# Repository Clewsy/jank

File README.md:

# jank

jank is **j**ust **an**other **k**eypad.  Specifically it is a USB numeric keypad with some macro buttons.  It's kind of an evolution of another project ([macro][link_gitlab_macr0]).

Additional photos and detail can be found at [clews.pro][link_clews_jank] and [hackaday.io][link_hackaday.io_jank].

Features include:
* Uses a USB type C connector (configured to identify as a USB 2.0 device).
* 21 keys total - 17 keys configured in a standard keypad arrangement, plus an addition row of four keys across the top.
* All 21 keys can be configured as any reguglar keyboard keystroke (including media control keys) or a programmable macro.
* The keys are all mechanical keyswitches - I used gateron blues which are pin-comnpatible with [Cherry MX][link_web_cherry_mx] keyswitches.
* All the keyswitches are plate-mounted with a laser-cut stainless steel plate.  The larger '+', '0' and "Enter" keys all have cherry-style, plate-mounted stabilizers.
* There is a 3mm led beneath each keyswitch so that the legends are all back-lit.
* The LEDs are powered via a boost controller (MP3202) which is enabled by a PWM signal from the microcontroller - this allows variable brightness.  Brightness is set by a tact switch on the bottom of the unit.  Pushing the switch cycles the LEDs from off through increasing levels of brightness and a pulsing effect with three different speeds.
* There is a single smd LED on the bottom of the unit that is programmed to function as the NUM LOCK indicator.

Although any key can be configured to function as any keystroke or macro, I use jank with my laptop as a traditional numerical keypad.  Only the top four keys are configured as macros.

Proudly mentioned at [hackaday.com][link_hackaday_jank].

*********************************

To do:

- [X] Hardware
    - [X] Parts selection.
    - [X] Schematic design.
    - [X] PCB layout design.
    - [X] Parts order.
    - [X] PCB assembly.
    - [X] Enclosure.
- [X] Firmware
    - [X] LED control.
    - [X] Regular keystrokes.
    - [X] Num lock LED.
    - [X] Simple macros.
    - [X] Complex macros.

*********************************

![The completed jank.][image_jank]

[link_clews_jank]:https://clews.pro/projects/jank.php
[link_gitlab_macr0]:https://gitlab.com/clewsy/macr0
[link_hackaday_jank]:https://hackaday.com/2021/06/08/custom-num-pad-does-double-duty-as-macro-pad/
[link_hackaday.io_jank]:https://hackaday.io/project/180104-jank
[link_web_cherry_mx]:https://www.cherrymx.de/en

[image_jank]:images/jank.jpg

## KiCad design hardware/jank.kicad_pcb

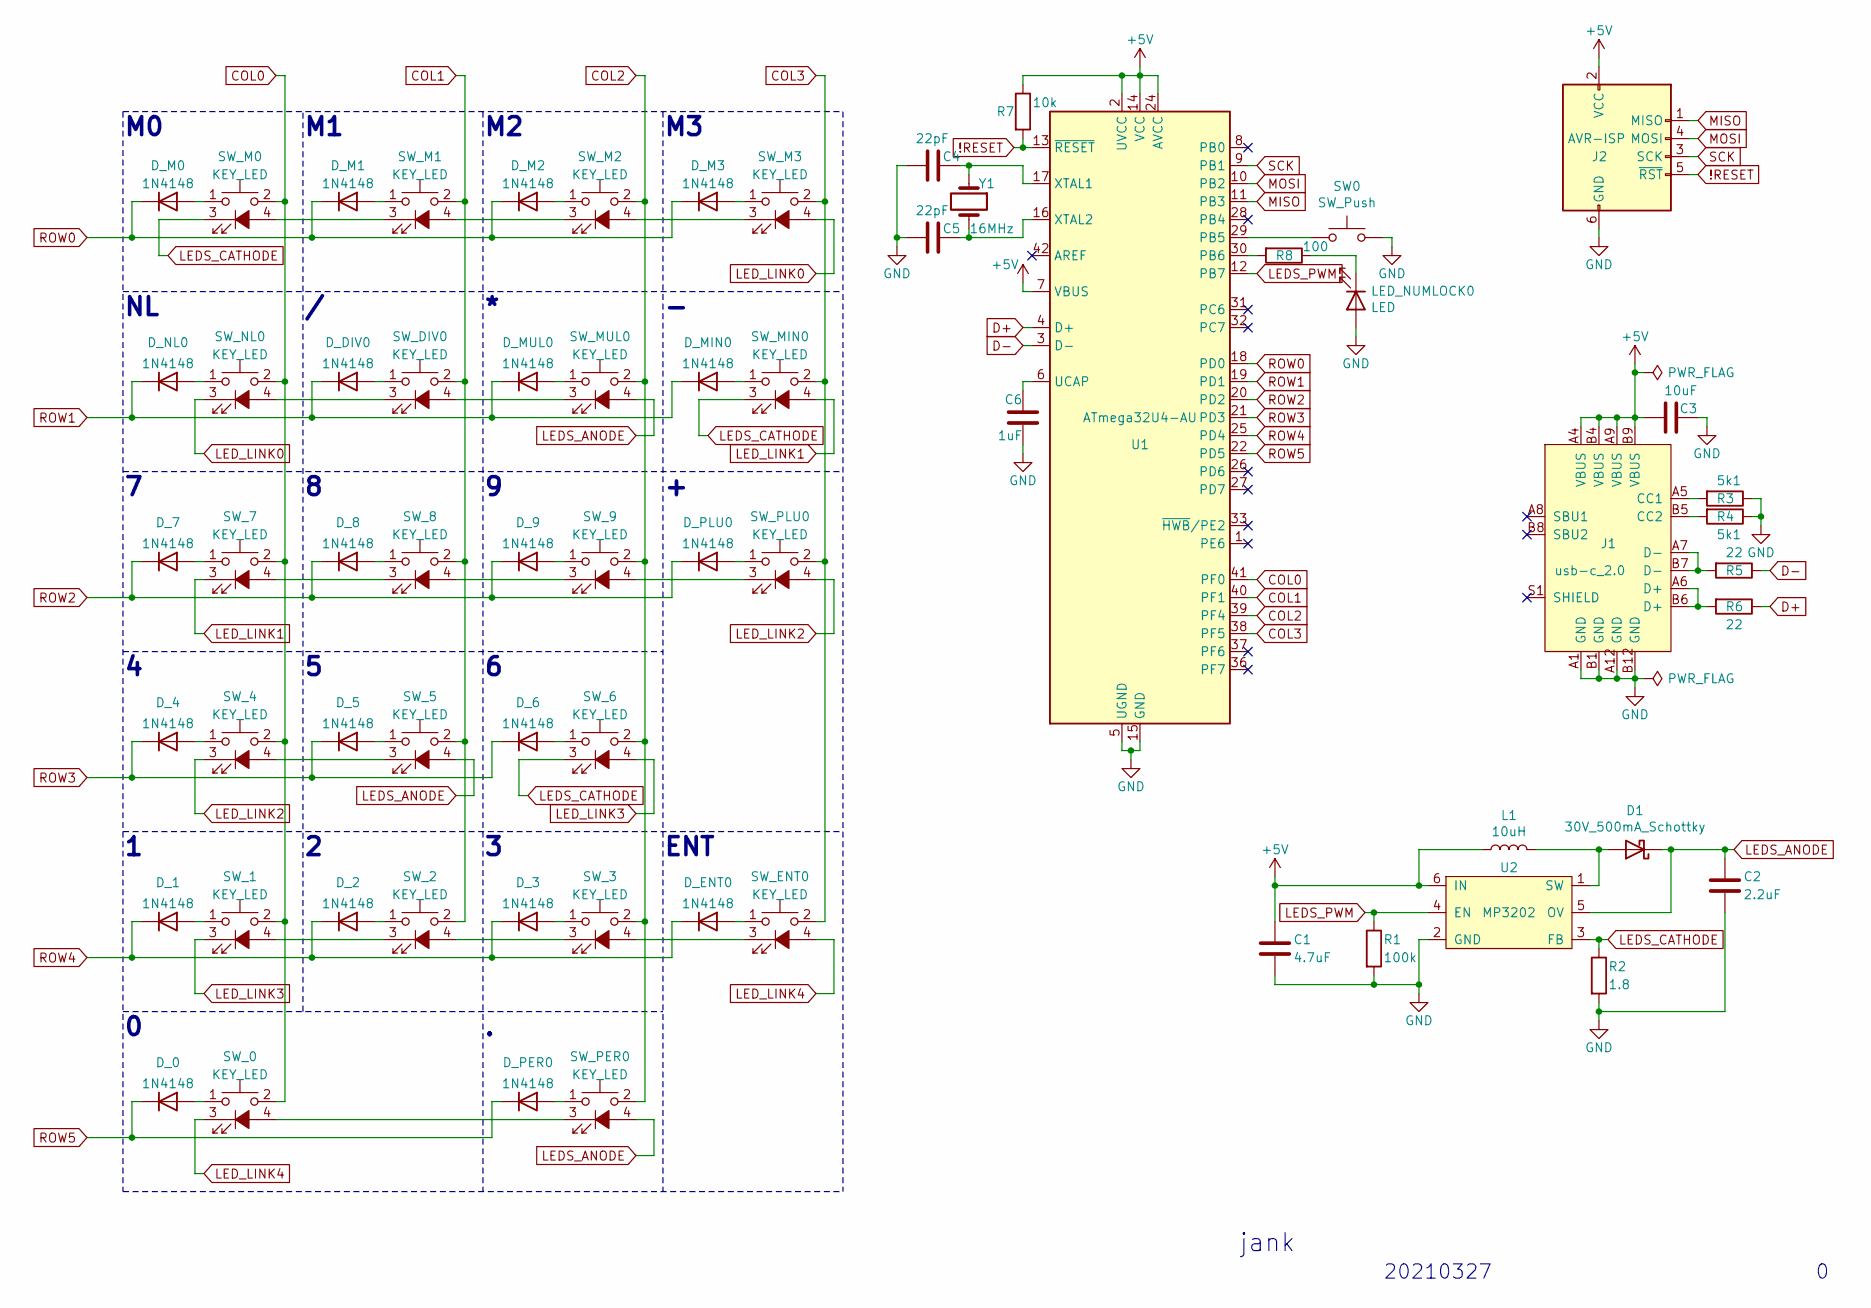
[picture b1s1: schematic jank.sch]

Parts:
C1: 4.7uF; C_1206_3216Metric_Pad1.42x1.75mm_HandSolder
C2: 2.2uF; C_1206_3216Metric_Pad1.42x1.75mm_HandSolder
C3: 10uF; C_1206_3216Metric_Pad1.42x1.75mm_HandSolder
C4, C5: 22pF; C_1206_3216Metric_Pad1.42x1.75mm_HandSolder
C6: 1uF; C_1206_3216Metric_Pad1.42x1.75mm_HandSolder
D1: 30V_500mA_Schottky; D_SOD-123
D_0, D_1, D_2, D_3, D_4, D_5, D_6, D_7, D_8, D_9: 1N4148; D_SOD-123
D_DIV0: 1N4148; D_SOD-123
D_ENT0: 1N4148; D_SOD-123
D_M0, D_M1, D_M2, D_M3: 1N4148; D_SOD-123
D_MIN0: 1N4148; D_SOD-123
D_MUL0: 1N4148; D_SOD-123
D_NL0: 1N4148; D_SOD-123
D_PER0: 1N4148; D_SOD-123
D_PLU0: 1N4148; D_SOD-123
J1: usb-c_2.0; USB_C_Receptacle_GCT_USB4085
J2: AVR-ISP; IDC-Header_2x03_P2.54mm_Vertical
L1: 10uH; SRN3010TA
LED_NUMLOCK0: LED; LED_Cree-XQ_HandSoldering
R1: 100k; R_1206_3216Metric_Pad1.42x1.75mm_HandSolder
R2: 1.8; R_1206_3216Metric_Pad1.42x1.75mm_HandSolder
R3, R4: 5k1; R_1206_3216Metric_Pad1.42x1.75mm_HandSolder
R5, R6: 22; R_1206_3216Metric_Pad1.42x1.75mm_HandSolder
R7: 10k; R_1206_3216Metric_Pad1.42x1.75mm_HandSolder
R8: 100; R_1206_3216Metric_Pad1.42x1.75mm_HandSolder
SW0: SW_Push; SW_Push_1P1T_NO_6x6mm_H9.5mm
SW_0, SW_1, SW_2, SW_3, SW_4, SW_5, SW_6, SW_7, SW_8, SW_9: KEY_LED; Gateron_LED_1.00u_Plate
SW_DIV0: KEY_LED; Gateron_LED_1.00u_Plate
SW_ENT0: KEY_LED; Gateron_LED_1.00u_Plate
SW_M0, SW_M1, SW_M2, SW_M3: KEY_LED; Gateron_LED_1.00u_Plate
SW_MIN0: KEY_LED; Gateron_LED_1.00u_Plate
SW_MUL0: KEY_LED; Gateron_LED_1.00u_Plate
SW_NL0: KEY_LED; Gateron_LED_1.00u_Plate
SW_PER0: KEY_LED; Gateron_LED_1.00u_Plate
SW_PLU0: KEY_LED; Gateron_LED_1.00u_Plate
U1: ATmega32U4-AU; TQFP-44_10x10mm_P0.8mm
U2: MP3202; SOT-23-6_Handsoldering
Y1: 16MHz; Crystal_SMD_HC49-SD

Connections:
!RESET: J2.5 (~RST), R7.2, U1.13 (~RESET)
+5V: C1.1, C3.1, J1.A4 (VBUS), J1.A9 (VBUS), J1.B4 (VBUS), J1.B9 (VBUS), J2.2 (VCC), L1.1, R7.1, U1.2 (UVCC), U1.7 (VBUS), U1.14 (VCC), U1.24 (AVCC), U1.34 (VCC), U1.44 (AVCC), U2.6 (IN)
COL0: SW_0.2, SW_1.2, SW_4.2, SW_7.2, SW_M0.2, SW_NL0.2, U1.41 (PF0)
COL1: SW_2.2, SW_5.2, SW_8.2, SW_DIV0.2, SW_M1.2, U1.40 (PF1)
COL2: SW_3.2, SW_6.2, SW_9.2, SW_M2.2, SW_MUL0.2, SW_PER0.2, U1.39 (PF4)
COL3: SW_ENT0.2, SW_M3.2, SW_MIN0.2, SW_PLU0.2, U1.38 (PF5)
D+: R6.1, U1.4 (D+)
D-: R5.1, U1.3 (D-)
GND: C1.2, C2.2, C3.2, C4.2, C5.2, C6.1, J1.A1 (GND), J1.A12 (GND), J1.B1 (GND), J1.B12 (GND), J2.6 (GND), LED_NUMLOCK0.2 (A), R1.2, R2.2, R3.1, R4.1, SW0.2, U1.5 (UGND), U1.15 (GND), U1.23 (GND), U1.35 (GND), U1.43 (GND), U2.2 (GND)
LEDS_ANODE: C2.1, D1.1 (K), SW_5.4 (A), SW_MUL0.4 (A), SW_PER0.4 (A), U2.5 (OV)
LEDS_CATHODE: R2.1, SW_6.3 (K), SW_M0.3 (K), SW_MIN0.3 (K), U2.3 (FB)
LEDS_PWM: R1.1, U1.12 (PB7), U2.4 (EN)
LED_LINK0: SW_M3.4 (A), SW_NL0.3 (K)
LED_LINK1: SW_7.3 (K), SW_MIN0.4 (A)
LED_LINK2: SW_4.3 (K), SW_PLU0.4 (A)
LED_LINK3: SW_1.3 (K), SW_6.4 (A)
LED_LINK4: SW_0.3 (K), SW_ENT0.4 (A)
MISO: J2.1 (MISO), U1.11 (PB3)
MOSI: J2.4 (MOSI), U1.10 (PB2)
unnamed: C4.1, U1.17 (XTAL1), Y1.1
unnamed: C5.1, U1.16 (XTAL2), Y1.2
unnamed: C6.2, U1.6 (UCAP)
unnamed: D1.2 (A), L1.2, U2.1 (SW)
unnamed: D_0.2 (A), SW_0.1
unnamed: D_1.2 (A), SW_1.1
unnamed: D_2.2 (A), SW_2.1
unnamed: D_3.2 (A), SW_3.1
unnamed: D_4.2 (A), SW_4.1
unnamed: D_5.2 (A), SW_5.1
unnamed: D_6.2 (A), SW_6.1
unnamed: D_7.2 (A), SW_7.1
unnamed: D_8.2 (A), SW_8.1
unnamed: D_9.2 (A), SW_9.1
unnamed: D_DIV0.2 (A), SW_DIV0.1
unnamed: D_ENT0.2 (A), SW_ENT0.1
unnamed: D_M0.2 (A), SW_M0.1
unnamed: D_M1.2 (A), SW_M1.1
unnamed: D_M2.2 (A), SW_M2.1
unnamed: D_M3.2 (A), SW_M3.1
unnamed: D_MIN0.2 (A), SW_MIN0.1
unnamed: D_MUL0.2 (A), SW_MUL0.1
unnamed: D_NL0.2 (A), SW_NL0.1
unnamed: D_PER0.2 (A), SW_PER0.1
unnamed: D_PLU0.2 (A), SW_PLU0.1
unnamed: J1.A5 (CC1), R3.2
unnamed: J1.A6 (D+), J1.B6 (D+), R6.2
unnamed: J1.A7 (D-), J1.B7 (D-), R5.2
unnamed: J1.B5 (CC2), R4.2
unnamed: LED_NUMLOCK0.1 (K), R8.1
unnamed: R8.2, U1.30 (PB6)
unnamed: SW0.1, U1.29 (PB5)
unnamed: SW_0.4 (A), SW_PER0.3 (K)
unnamed: SW_1.4 (A), SW_2.3 (K)
unnamed: SW_2.4 (A), SW_3.3 (K)
unnamed: SW_3.4 (A), SW_ENT0.3 (K)
unnamed: SW_4.4 (A), SW_5.3 (K)
unnamed: SW_7.4 (A), SW_8.3 (K)
unnamed: SW_8.4 (A), SW_9.3 (K)
unnamed: SW_9.4 (A), SW_PLU0.3 (K)
unnamed: SW_DIV0.3 (K), SW_NL0.4 (A)
unnamed: SW_DIV0.4 (A), SW_MUL0.3 (K)
unnamed: SW_M0.4 (A), SW_M1.3 (K)
unnamed: SW_M1.4 (A), SW_M2.3 (K)
unnamed: SW_M2.4 (A), SW_M3.3 (K)
ROW0: D_M0.1 (K), D_M1.1 (K), D_M2.1 (K), D_M3.1 (K), U1.18 (PD0)
ROW1: D_DIV0.1 (K), D_MIN0.1 (K), D_MUL0.1 (K), D_NL0.1 (K), U1.19 (PD1)
ROW2: D_7.1 (K), D_8.1 (K), D_9.1 (K), D_PLU0.1 (K), U1.20 (PD2)
ROW3: D_4.1 (K), D_5.1 (K), D_6.1 (K), U1.21 (PD3)
ROW4: D_1.1 (K), D_2.1 (K), D_3.1 (K), D_ENT0.1 (K), U1.25 (PD4)
ROW5: D_0.1 (K), D_PER0.1 (K), U1.22 (PD5)
SCK: J2.3 (SCK), U1.9 (PB1)

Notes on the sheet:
ENT
jank
20210327

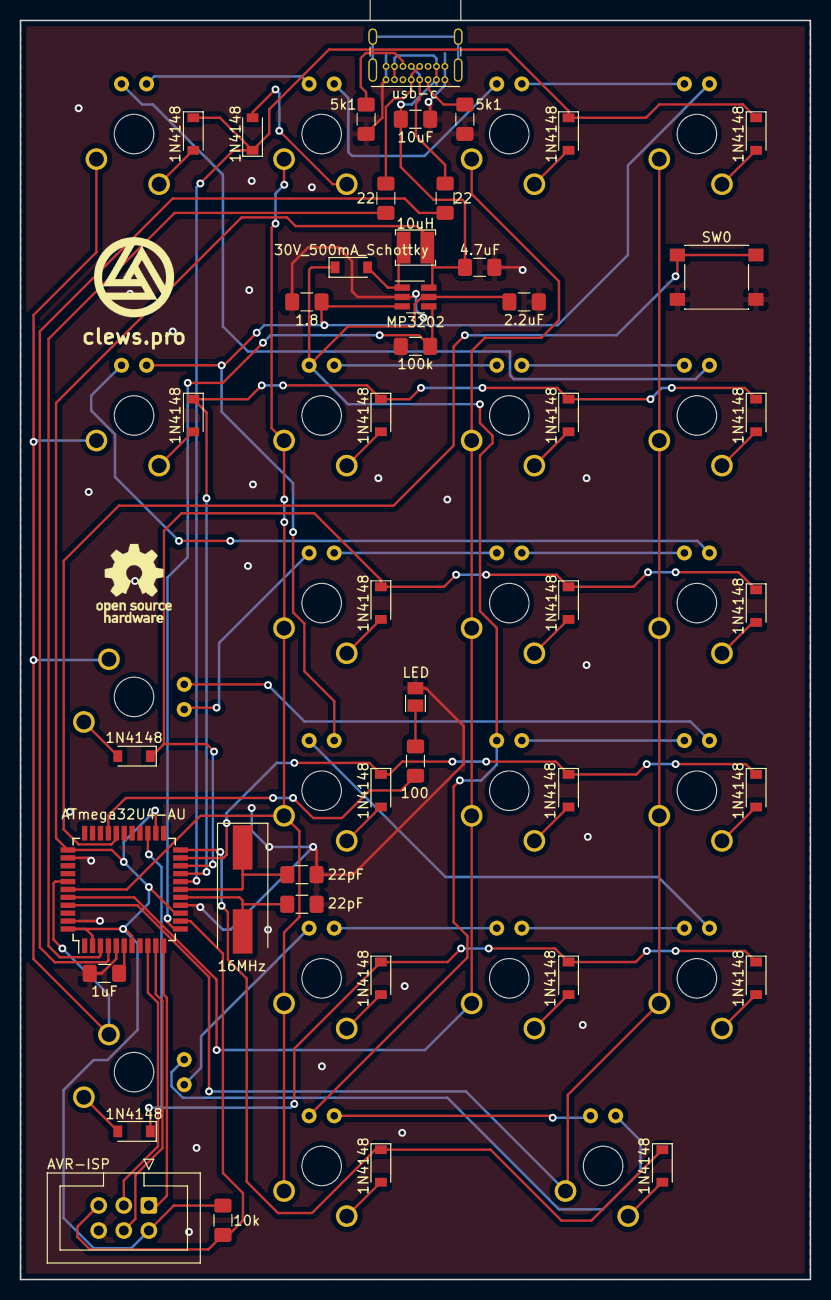
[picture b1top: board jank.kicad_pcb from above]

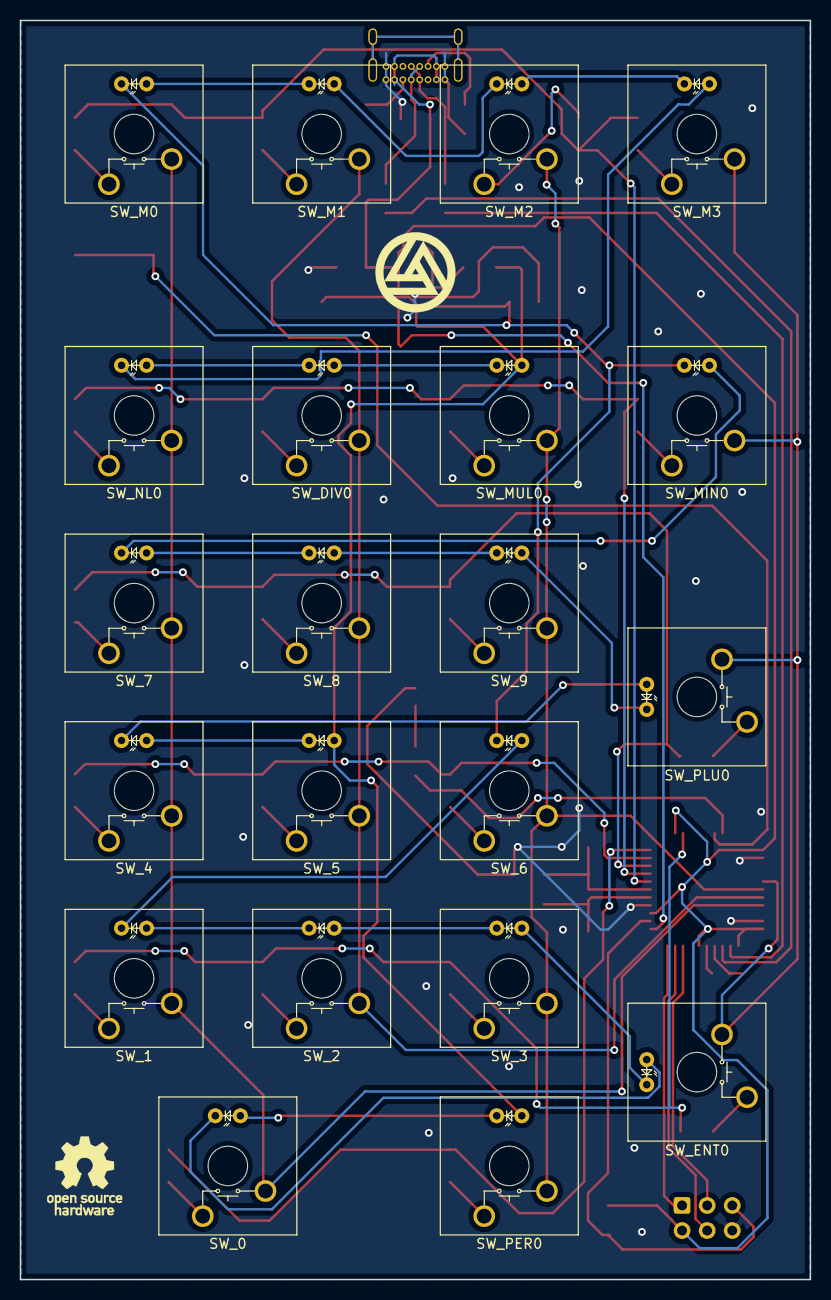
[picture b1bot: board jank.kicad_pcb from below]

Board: 2 copper layers, 80.0 x 127.5 mm, 65 parts (21 on the bottom side), 71 nets.

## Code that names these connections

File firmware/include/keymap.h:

#include <avr/pgmspace.h>	// Required for writing to and reading from program memory space.

// Define microcontroller registers for configuring inputs and outputs as required for keypad scanning.
#define ROWS_PORT	PORTD
#define ROWS_DDR	DDRD
#define ROWS_PINS	PIND
#define COLS_PORT	PORTF
#define COLS_DDR	DDRF
#define COLS_PINS	PINF

// Define which physical microcontroller pins are conncted to the keypad rows and columns.
#define ROW0	PD0
#define ROW1	PD1
#define ROW2	PD2
#define ROW3	PD3
#define ROW4	PD4
#define ROW5	PD5
#define COL0	PF0
#define COL1	PF1
#define COL2	PF4
#define COL3	PF5
// !IMPORTANT! - By default, the JTAGEN (JTAG enable) bit is set (i.e. actually value zero which means enabled in the land of AVR
// fuse bytes).  It must be cleared (i.e. set to 1!) otherwise PF4 and PF5 cannot be used as GPIO.  Out of the box the AtMega32U4
// low fuse (lfuse) byte was set to 0x99.  Writing  this to 0xD9 disabled JTAG. 

// Maximum number of rows and columns that should be identified as regular keystrokes or macros.
#define MAX_NUM_KEY_ROWS	6
#define MAX_NUM_KEY_COLS	4
#define MAX_NUM_MACRO_ROWS	6
#define MAX_NUM_MACRO_COLS	4

// If the number of characters in a macro string defined in keymap.c exceeds this value, the macro will be truncated.
#define MAX_MACRO_CHARS		40
#define MAX_MACRO_ACTIONS	20

// Identifiers used with macro_t (m_action element) to determine what to do with the macro_t array element.
#define M_NULL	        0x00
#define M_STRING	0x01	// If macro->m_action = M_STRING, then macro->m_array is a character string to be typed.
#define M_KEYS		0x02	// If macro->m_action = M_KEYS, then macro->m_array is combination of keys to be pressed.
#define M_WAIT          0x03	// If macro->m_action = M_WAIT, then macro->m_array is an array of integer seconds to pause.

// Define the structure of a macro.  The macros are actually defined as an array of type macro_t so that multiple macros can be
// run sequentially with a single keypress.
typedef struct {
	uint8_t m_action;
	char m_array[MAX_MACRO_CHARS];  // m_array is interpreted differently depending on the value of m_action.  See above.
} macro_t;


// Declare the key-to-pin, macro-to-pin, keymap and macromap arrays.
extern const uint8_t key_row_array[MAX_NUM_KEY_ROWS];
extern const uint8_t key_col_array[MAX_NUM_KEY_COLS];
extern const uint8_t macro_row_array[MAX_NUM_MACRO_ROWS];
extern const uint8_t macro_col_array[MAX_NUM_MACRO_COLS];
extern const char KEYMAP[MAX_NUM_KEY_ROWS][MAX_NUM_KEY_COLS];
extern const macro_t MACROMAP[MAX_NUM_MACRO_ROWS][MAX_NUM_MACRO_COLS][MAX_MACRO_ACTIONS];

// Key scan-codes:
// Note these are defined in the lufa library file LUFA/Drivers/USB/Class/Common/HIDClassCommon.h but repeated again
// here for convenience.
#define HID_KEYBOARD_SC_RESERVED				0x00
#define HID_KEYBOARD_SC_ERROR_ROLLOVER				0x01
#define HID_KEYBOARD_SC_POST_FAIL				0x02
#define HID_KEYBOARD_SC_ERROR_UNDEFINED				0x03
#define HID_KEYBOARD_SC_A					0x04
#define HID_KEYBOARD_SC_B					0x05
#define HID_KEYBOARD_SC_C					0x06
#define HID_KEYBOARD_SC_D					0x07
#define HID_KEYBOARD_SC_E					0x08
#define HID_KEYBOARD_SC_F					0x09
#define HID_KEYBOARD_SC_G					0x0A
#define HID_KEYBOARD_SC_H					0x0B
#define HID_KEYBOARD_SC_I					0x0C
#define HID_KEYBOARD_SC_J					0x0D
#define HID_KEYBOARD_SC_K					0x0E
#define HID_KEYBOARD_SC_L					0x0F
#define HID_KEYBOARD_SC_M					0x10
#define HID_KEYBOARD_SC_N					0x11
#define HID_KEYBOARD_SC_O					0x12
#define HID_KEYBOARD_SC_P					0x13
#define HID_KEYBOARD_SC_Q					0x14
#define HID_KEYBOARD_SC_R					0x15
#define HID_KEYBOARD_SC_S					0x16
#define HID_KEYBOARD_SC_T					0x17
#define HID_KEYBOARD_SC_U					0x18
#define HID_KEYBOARD_SC_V					0x19
#define HID_KEYBOARD_SC_W					0x1A
#define HID_KEYBOARD_SC_X					0x1B
#define HID_KEYBOARD_SC_Y					0x1C
#define HID_KEYBOARD_SC_Z					0x1D
#define HID_KEYBOARD_SC_1_AND_EXCLAMATION			0x1E
#define HID_KEYBOARD_SC_2_AND_AT				0x1F
#define HID_KEYBOARD_SC_3_AND_HASHMARK				0x20
#define HID_KEYBOARD_SC_4_AND_DOLLAR				0x21
#define HID_KEYBOARD_SC_5_AND_PERCENTAGE			0x22
#define HID_KEYBOARD_SC_6_AND_CARET				0x23
#define HID_KEYBOARD_SC_7_AND_AMPERSAND				0x24
#define HID_KEYBOARD_SC_8_AND_ASTERISK				0x25
#define HID_KEYBOARD_SC_9_AND_OPENING_PARENTHESIS		0x26
#define HID_KEYBOARD_SC_0_AND_CLOSING_PARENTHESIS		0x27
#define HID_KEYBOARD_SC_ENTER					0x28
#define HID_KEYBOARD_SC_ESCAPE					0x29
#define HID_KEYBOARD_SC_BACKSPACE				0x2A
#define HID_KEYBOARD_SC_TAB					0x2B
#define HID_KEYBOARD_SC_SPACE					0x2C
#define HID_KEYBOARD_SC_MINUS_AND_UNDERSCORE			0x2D
#define HID_KEYBOARD_SC_EQUAL_AND_PLUS				0x2E
#define HID_KEYBOARD_SC_OPENING_BRACKET_AND_OPENING_BRACE	0x2F
#define HID_KEYBOARD_SC_CLOSING_BRACKET_AND_CLOSING_BRACE	0x30
#define HID_KEYBOARD_SC_BACKSLASH_AND_PIPE			0x31
#define HID_KEYBOARD_SC_NON_US_HASHMARK_AND_TILDE		0x32
#define HID_KEYBOARD_SC_SEMICOLON_AND_COLON			0x33
#define HID_KEYBOARD_SC_APOSTROPHE_AND_QUOTE			0x34
#define HID_KEYBOARD_SC_GRAVE_ACCENT_AND_TILDE			0x35
#define HID_KEYBOARD_SC_COMMA_AND_LESS_THAN_SIGN		0x36
#define HID_KEYBOARD_SC_DOT_AND_GREATER_THAN_SIGN		0x37
#define HID_KEYBOARD_SC_SLASH_AND_QUESTION_MARK			0x38
#define HID_KEYBOARD_SC_CAPS_LOCK				0x39
#define HID_KEYBOARD_SC_F1					0x3A
#define HID_KEYBOARD_SC_F2					0x3B
#define HID_KEYBOARD_SC_F3					0x3C
#define HID_KEYBOARD_SC_F4					0x3D
#define HID_KEYBOARD_SC_F5					0x3E
#define HID_KEYBOARD_SC_F6					0x3F
#define HID_KEYBOARD_SC_F7					0x40
#define HID_KEYBOARD_SC_F8					0x41
#define HID_KEYBOARD_SC_F9					0x42
#define HID_KEYBOARD_SC_F10					0x43
#define HID_KEYBOARD_SC_F11					0x44
#define HID_KEYBOARD_SC_F12					0x45
#define HID_KEYBOARD_SC_PRINT_SCREEN				0x46
#define HID_KEYBOARD_SC_SCROLL_LOCK				0x47
#define HID_KEYBOARD_SC_PAUSE					0x48
#define HID_KEYBOARD_SC_INSERT					0x49
#define HID_KEYBOARD_SC_HOME					0x4A
#define HID_KEYBOARD_SC_PAGE_UP					0x4B
#define HID_KEYBOARD_SC_DELETE					0x4C
#define HID_KEYBOARD_SC_END					0x4D
#define HID_KEYBOARD_SC_PAGE_DOWN				0x4E
#define HID_KEYBOARD_SC_RIGHT_ARROW				0x4F
#define HID_KEYBOARD_SC_LEFT_ARROW				0x50
#define HID_KEYBOARD_SC_DOWN_ARROW				0x51
#define HID_KEYBOARD_SC_UP_ARROW				0x52
#define HID_KEYBOARD_SC_NUM_LOCK				0x53
#define HID_KEYBOARD_SC_KEYPAD_SLASH				0x54
#define HID_KEYBOARD_SC_KEYPAD_ASTERISK				0x55
#define HID_KEYBOARD_SC_KEYPAD_MINUS				0x56
#define HID_KEYBOARD_SC_KEYPAD_PLUS				0x57
#define HID_KEYBOARD_SC_KEYPAD_ENTER				0x58
#define HID_KEYBOARD_SC_KEYPAD_1_AND_END			0x59
#define HID_KEYBOARD_SC_KEYPAD_2_AND_DOWN_ARROW			0x5A
#define HID_KEYBOARD_SC_KEYPAD_3_AND_PAGE_DOWN			0x5B
#define HID_KEYBOARD_SC_KEYPAD_4_AND_LEFT_ARROW			0x5C
#define HID_KEYBOARD_SC_KEYPAD_5				0x5D
#define HID_KEYBOARD_SC_KEYPAD_6_AND_RIGHT_ARROW		0x5E
#define HID_KEYBOARD_SC_KEYPAD_7_AND_HOME			0x5F
#define HID_KEYBOARD_SC_KEYPAD_8_AND_UP_ARROW			0x60
#define HID_KEYBOARD_SC_KEYPAD_9_AND_PAGE_UP			0x61
#define HID_KEYBOARD_SC_KEYPAD_0_AND_INSERT			0x62
#define HID_KEYBOARD_SC_KEYPAD_DOT_AND_DELETE			0x63
#define HID_KEYBOARD_SC_NON_US_BACKSLASH_AND_PIPE		0x64
#define HID_KEYBOARD_SC_APPLICATION				0x65

#define HID_KEYBOARD_SC_LEFT_CONTROL				0xE0
#define HID_KEYBOARD_SC_LEFT_SHIFT				0xE1
#define HID_KEYBOARD_SC_LEFT_ALT				0xE2
#define HID_KEYBOARD_SC_LEFT_GUI				0xE3
#define HID_KEYBOARD_SC_RIGHT_CONTROL				0xE4
#define HID_KEYBOARD_SC_RIGHT_SHIFT				0xE5
#define HID_KEYBOARD_SC_RIGHT_ALT				0xE6
#define HID_KEYBOARD_SC_RIGHT_GUI				0xE7

#define HID_MEDIACONTROLLER_SC_PLAY				0xF0
#define HID_MEDIACONTROLLER_SC_PAUSE				0xF1
#define HID_MEDIACONTROLLER_SC_FAST_FORWARD			0xF2
#define HID_MEDIACONTROLLER_SC_REWIND				0xF3
#define HID_MEDIACONTROLLER_SC_NEXT				0xF4
#define HID_MEDIACONTROLLER_SC_PREVIOUS				0xF5
#define HID_MEDIACONTROLLER_SC_STOP				0xF6
#define HID_MEDIACONTROLLER_SC_TOGGLE				0xF7
#define HID_MEDIACONTROLLER_SC_MUTE				0xF8
#define HID_MEDIACONTROLLER_SC_VOLUME_UP			0xF9
#define HID_MEDIACONTROLLER_SC_VOLUME_DOWN			0xFA

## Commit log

2021-03-07 Repo creation. Just some datasheets.
2021-03-07 Basic readme - detail to be added later.
2021-03-08 Begun working on the schematic.
2021-03-08 Added diode spec.
2021-03-08 Rev_0 schematic finished, first pass at PCB layout (no traces yet).
2021-03-08 Run traces and fills.
2021-03-08 Started tidy up (silk screen etc).
2021-03-12 Moved led pins to port B. Added push-button on port B. Reworked layout to suit these changes.
2021-03-13 Cleaned up rev 0 PCB layout, ordered fabrication. Added .gitignore.
2021-03-14 Added pdf of schematic.
2021-03-26 Renaming project and repo from numpty to jank.
2021-03-26 Updated readme to show new project name.
2021-03-27 Partially assembled. Testing with code from macr0 - just configured to test LED pulsing, no USB yet.
2021-03-27 Datasheet for the smd LED.
2021-03-28 Works as a keypad! Took a while to learn that jtag was enabled by default thus disabling GPIO on PF4 and PF5.
2021-03-28 SMD LED now acts as numlock indicator. Some comments and tidy-up.
2021-03-28 Adjusted de-bounce. Comments.
2021-03-28 What a dummy, the LED was backwards.
2021-03-28 Tested media keys.
2021-03-28 Macros are working (at least simple character string macros).
2021-03-31 Work on the readme.
2021-03-31 Trying to get markdown indented checkboxes to render.
2021-04-03 Experimenting with more complicated macros. Created macro_t type. Can now send multiple strings.
2021-04-04 Can now type strings or combination keystrokes. Lots of room for efficiency though.
2021-04-04 Added vscode c/c++ properties for improved intellisense.
2021-04-04 Macros can now include delays.
2021-04-04 Macros seem to be working pretty well. Tidy-up and comments.
2021-04-04 Defaults.
2021-04-04 More comments.
2021-04-04 Formatting and comments.
2021-04-04 Comment.
2021-04-04 Timings.
2021-04-04 Build finished (or at least working).
2021-04-04 Missing X
2021-04-04 Aded a photo.
2021-04-04 Fixed image.
2021-04-25 Changed ifs to switch/case. Fixed media control key op. Changed default enabled keymaps.
2021-05-30 Rogue space.
2021-06-01 Extra info and hackaday.io link.
2021-06-10 Added hackaday article link.
